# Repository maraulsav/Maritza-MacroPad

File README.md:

## Maritza-MacroPad
Maritza's MacroPad
This is my first ever PCB project. Currently I am making a MacroPad that capable of braille keys and adjusting the volume
It consist of 9 keys MacroPad with a rotary encoder and 2 WS2812B Leds

## Features : 
- Dual layer acrylic case.
- EC11 Rotary encoder
- 2 WS2812B RGB LEDs.
- 9 keys

## CAD Model:
Made in Fusion360
I think it need to used 4 M3 Bolts, 2 M2.5 Bolts (For the mounting hole in the rotary encoder-PCB, I am actually not sure in this part)
and heatset insert. 

## PCB
Here's my PCB! It was made in KiCad
I used matrix method for the keys, I followed the guide from GitHub repos dumbpad
These are the Foot Print I used 
- Rotary_Encoder: Rotary Encoder_Alps_EC11E-Switch_Vertical_H20mm_CircularMounting Holes
- Diode: Diode_THT:D_DO-35_SOD27_P7.62mm_Horizontal
- XIAO RP2040: Seeed Studio XIAO Series Library: XIAO-RP2040-DIP
- Push Button: Button_Switch_Keyboard: SW_Cherry_MX_1.00u_PCB
- SK6812MINI: LED SMD: LED_SK6812MINI_PLCC4_3.5x3.5mm_P1.75mm

Schematic 

PCB

## Firmware Overview
This MacroPad uses the KMK Firmware -- python in VS Code
- The rotary encoder changes volume. press to mute
- The center column keys is function as delete, enter, space (concurrently from top to bottom)
- The right and left column key is the one that function like braille

## BOM:
Here should be everything you need to make this HackPad
- 4x Cherry MX Switches
- 4x DSA Keycaps
- 9x 1N4148 DO-35 Diodes.
- 2x WS2812B LEDs
- 1x EC11 Rotary Encoder
- 1x XIAO RP2040
- 1x Case (2 Printed Parts)
- 4x Heatsocket
- 4x M3x16mm SHCS Bolts
- 2x M2.5 Bolts

# Extra stuff
I hope this can works out hwhwhw and later perhaps I can donate it to people that have difficulties in hearing or seeing. 
I think it will be more easy to them to just like having keyboard that capable of braille

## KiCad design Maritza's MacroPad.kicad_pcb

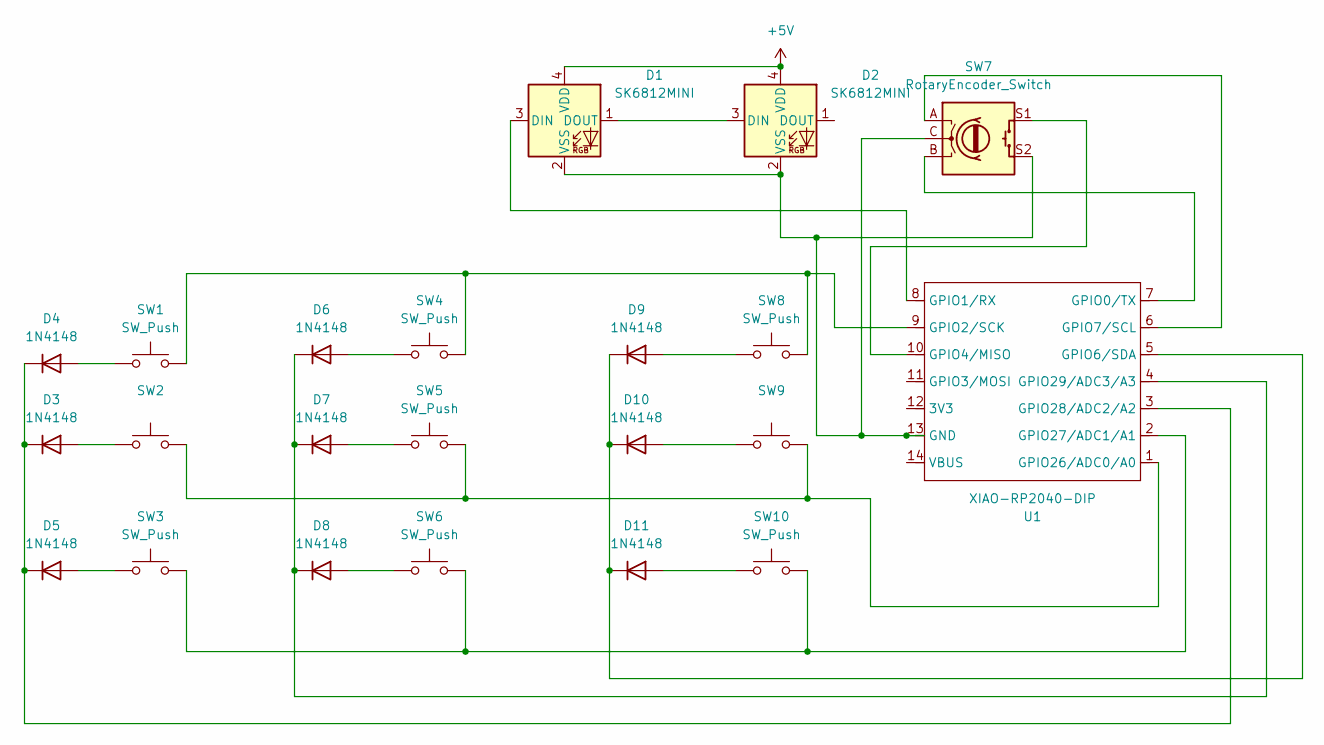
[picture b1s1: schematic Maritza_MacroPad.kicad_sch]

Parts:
D1, D2: SK6812MINI; LED_SK6812MINI_PLCC4_3.5x3.5mm_P1.75mm
D3, D4, D5, D6, D7, D8, D9, D10, D11: 1N4148; D_DO-35_SOD27_P7.62mm_Horizontal
SW1, SW2, SW3, SW4, SW5, SW6, SW8, SW9, SW10: SW_Push; SW_Cherry_MX_1.00u_PCB
SW7: RotaryEncoder_Switch; RotaryEncoder_Alps_EC11E-Switch_Vertical_H20mm_CircularMoun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
U1: XIAO-RP2040-DIP

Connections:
+5V: D1.4 (VDD), D2.4 (VDD)
unnamed: D1.3 (DIN), U1.8 (GPIO1/RX)
unnamed: D1.1 (DOUT), D2.3 (DIN)
unnamed: D1.2 (VSS), D2.2 (VSS), SW7.C, SW7.S2, U1.13 (GND)
unnamed: D3.2 (A), SW2.1
unnamed: D3.1 (K), D4.1 (K), D5.1 (K), U1.3 (GPIO28/ADC2/A2)
unnamed: D4.2 (A), SW1.1
unnamed: D5.2 (A), SW3.1
unnamed: D6.2 (A), SW4.1
unnamed: D6.1 (K), D7.1 (K), D8.1 (K), U1.4 (GPIO29/ADC3/A3)
unnamed: D7.2 (A), SW5.1
unnamed: D8.2 (A), SW6.1
unnamed: D9.2 (A), SW8.1
unnamed: D10.2 (A), SW9.1
unnamed: D9.1 (K), D10.1 (K), D11.1 (K), U1.5 (GPIO6/SDA)
unnamed: D11.2 (A), SW10.1
unnamed: SW7.B, U1.7 (GPIO0/TX)
unnamed: SW1.2, SW4.2, SW8.2, U1.9 (GPIO2/SCK)
unnamed: SW7.S1, U1.10 (GPIO4/MISO)
unnamed: SW7.A, U1.6 (GPIO7/SCL)
unnamed: SW2.2, SW5.2, SW9.2, U1.1 (GPIO26/ADC0/A0)
unnamed: SW3.2, SW6.2, SW10.2, U1.2 (GPIO27/ADC1/A1)

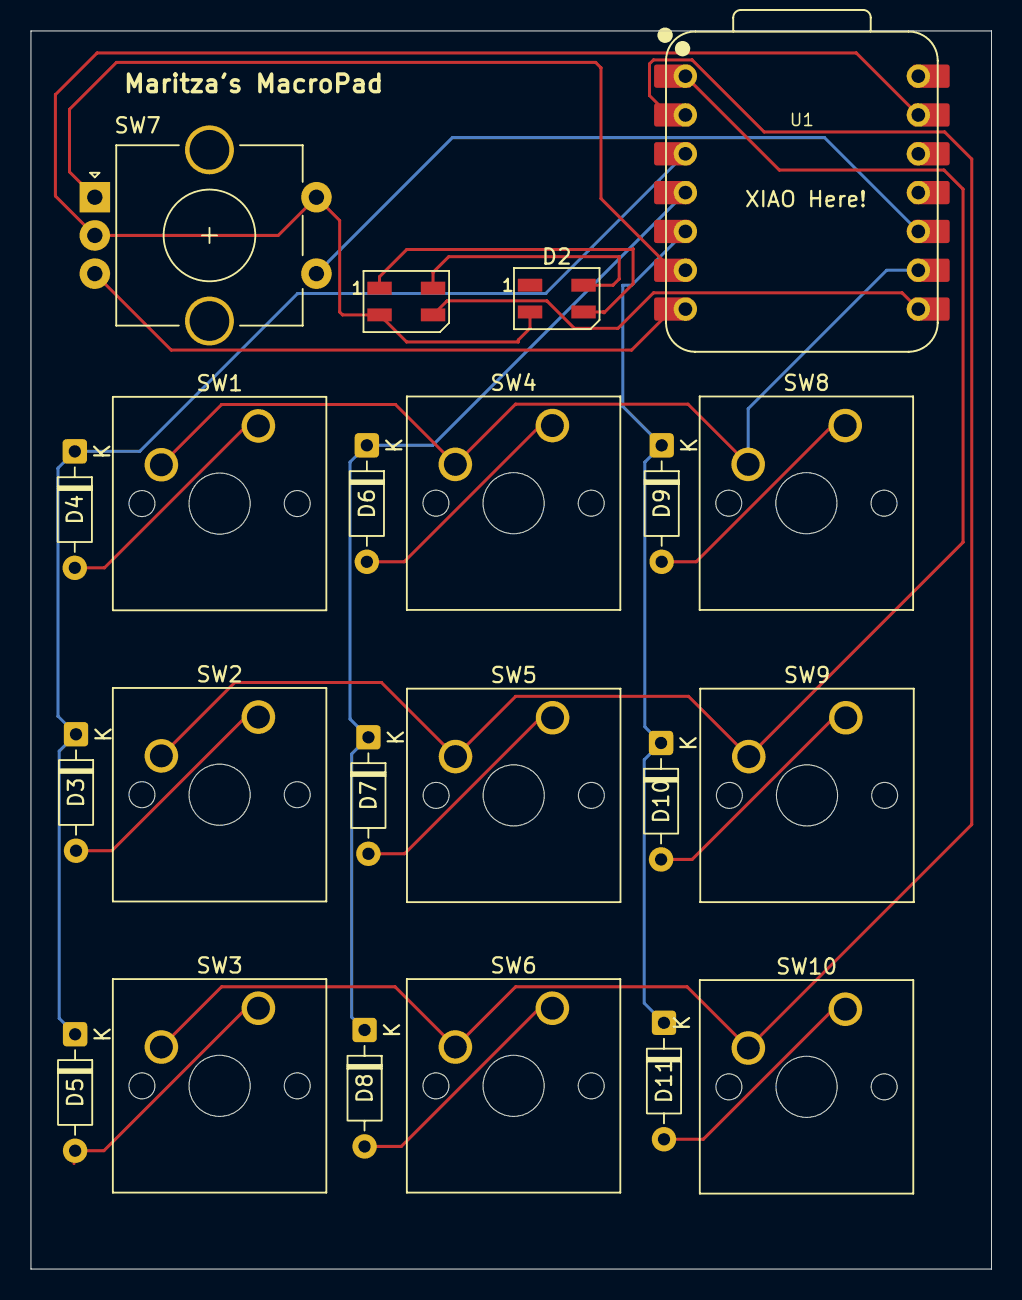
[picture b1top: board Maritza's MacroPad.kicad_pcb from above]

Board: 2 copper layers, 62.8 x 81.0 mm, 22 parts (0 on the bottom side), 22 nets.

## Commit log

2025-12-24 Organize Folders
